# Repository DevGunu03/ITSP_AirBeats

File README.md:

# AirBeats
Express your inner artist (and demons)

## Members
- Shobhit Maheshwari
- Harsh Agarwal
- Archit Swamy
- Kartik UC

Datasheets and other info: https://drive.google.com/drive/folders/13BC71OeGT-9EMUbr2pCwrsLQNoBRDwO7?usp=sharing

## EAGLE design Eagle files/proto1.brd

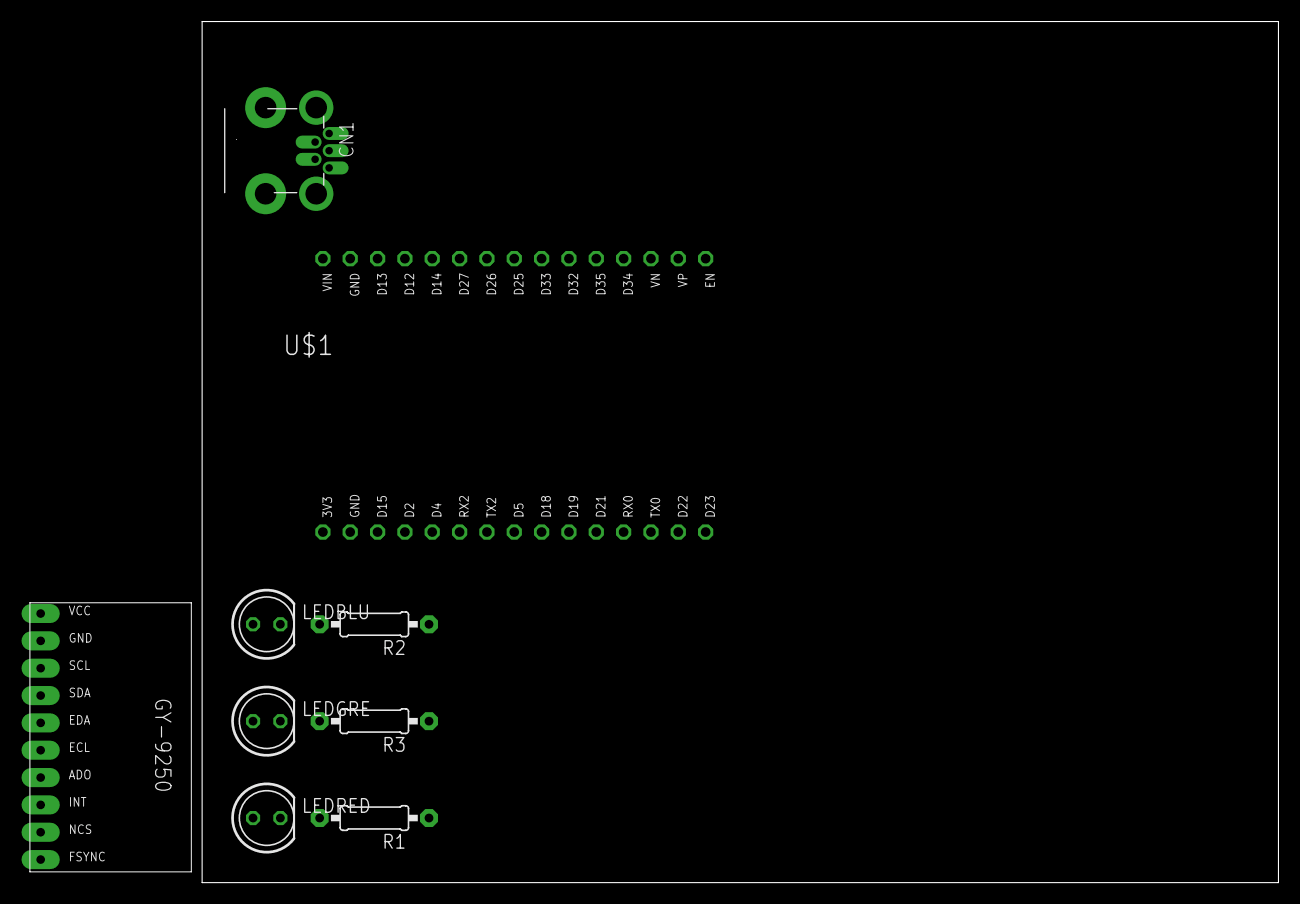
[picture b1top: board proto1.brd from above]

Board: 2 copper layers, 100.0 x 80.0 mm, 9 parts (0 on the bottom side), 10 nets, no tracks yet.

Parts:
CN1: USB-MINIB-THM
LEDBLU: LED5MM
LEDGRE: LED5MM
LEDRED: LED5MM
R1, R2, R3: 0207/10
U$1: ESP32_DEVKIT
U$2: GY-9250

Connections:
GND: CN1.GND, U$1.GND@1, U$1.GND@2, U$2.GND
LEDBLU: R2.1, U$1.D35
LEDGRE: R3.1, U$1.D32
LEDRED: R1.1, U$1.D34
unnamed: LEDRED.K, R1.2
unnamed: LEDBLU.K, R2.2
unnamed: LEDGRE.K, R3.2
SCL: U$1.D22, U$2.SCL
SDA: U$1.D21, U$2.SDA
VCC: CN1.VBUS, LEDBLU.A, LEDGRE.A, LEDRED.A, U$1.3V3, U$2.VCC

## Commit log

2022-06-07 Add Eagle files
2022-06-07 Add LEDs to board
2022-06-07 Change microcontroller
2022-06-07 Add nets
2022-06-07 Add SW files
2022-06-07 Rearrange SW files
2022-06-07 Add quaternion code
2022-07-05 Add MATLAB files for sensor bias
2022-07-05 Clean up plots
2022-07-05 Add drift remover suggestion
2022-07-06 Add 3D model
2022-07-11 linear interpolation for angular velocities
2022-07-12 Add sample communication files
2022-07-13 Add bluetooth communication code
2022-07-13 Add final holder model
2022-07-13 Add interface and transmission code
2022-07-13 Add time label
2022-07-13 Add MPU-9250
2022-07-14 A cruddy, but working kalman filter. compile sensorbias>>kalmn>>model. apologies for lack of organisation.
2022-07-14 Add BT files
2022-07-25 Make progress
2022-07-26 Add calibration data
2022-07-26 kalman test
2022-07-27 Fix orientation
2022-07-27 Add drums
2022-07-29 Link drum sounds
2022-07-30 Add a lot of calibration data
2022-07-30 Add async data collection
2022-07-31 filter accel data 1.0
2022-07-31 accel data filter 1.0
2022-07-31 kalman 1.0
2022-08-01 minor changes to kalman9250
2022-08-03 Add calibration
